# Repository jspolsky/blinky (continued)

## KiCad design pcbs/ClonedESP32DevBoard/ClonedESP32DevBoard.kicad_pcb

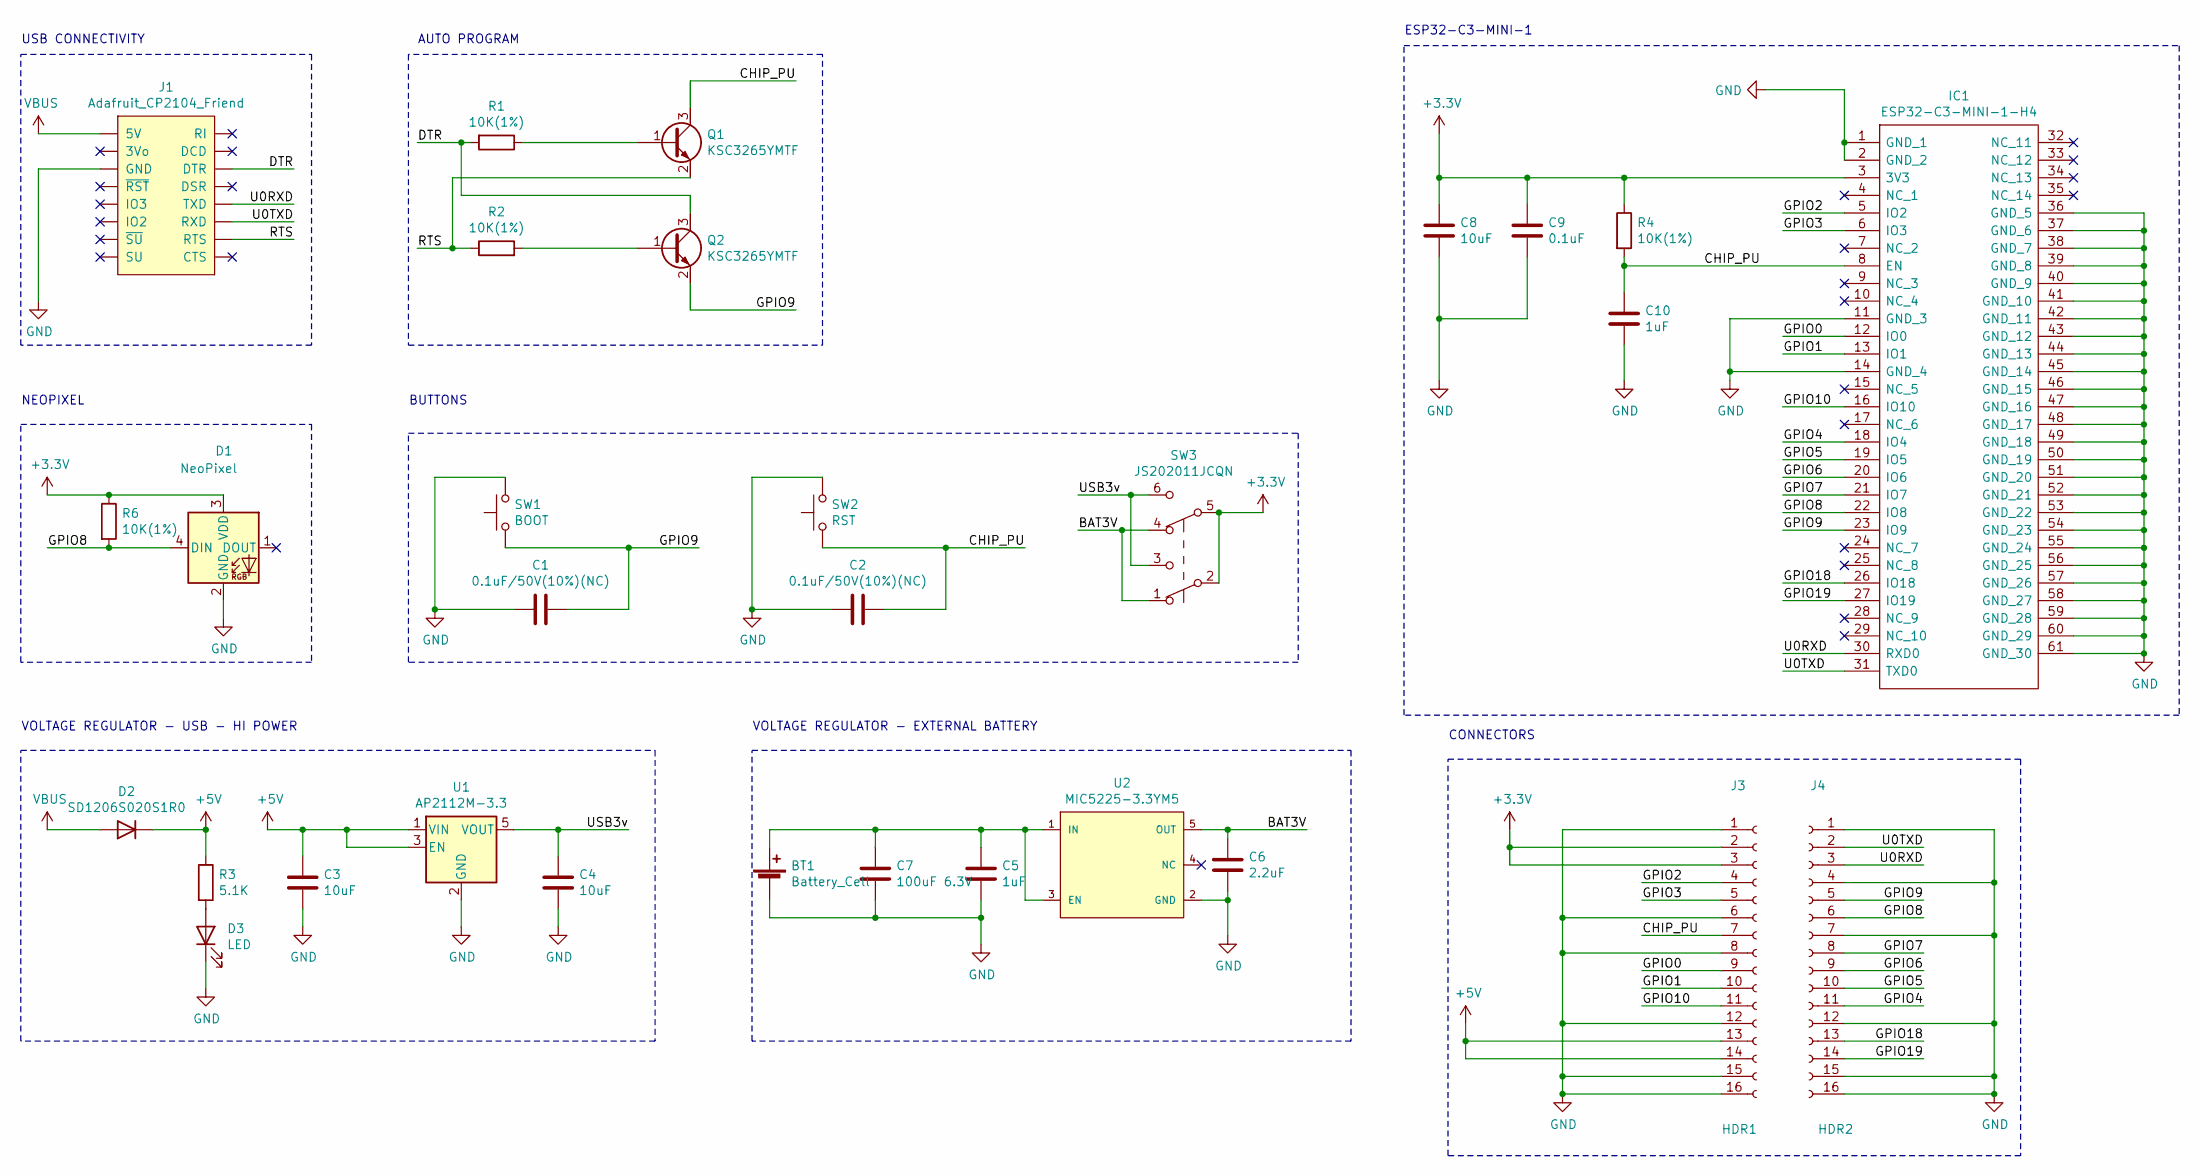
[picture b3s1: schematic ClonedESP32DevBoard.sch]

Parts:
BT1: Battery_Cell; PinHeader_1x02_P2.54mm_Vertical
C1, C2: 0.1uF/50V(10%)(NC); C_0805_2012Metric
C3, C4, C8: 10uF; C_0805_2012Metric
C5, C10: 1uF; C_0805_2012Metric
C6: 2.2uF; C_0805_2012Metric
C7: 100uF 6.3V; C_1210_3225Metric
C9: 0.1uF; C_0805_2012Metric
D1: NeoPixel; LED_WS2812-2020
D2: SD1206S020S1R0‎; D_1206_3216Metric
D3: LED; LED_0805_2012Metric
IC1: ESP32-C3-MINI-1-H4; ESP32-C3-MINI-1; Manufacturer_Part_Number ESP32-C3-MINI-1-H4; Mouser Part Number 356-ESP32-C3-MINI1H4
J1: Adafruit_CP2104_Friend
J3: HDR1; PinHeader_1x16_P2.54mm_Vertical
J4: HDR2; PinHeader_1x16_P2.54mm_Vertical
Q1, Q2: KSC3265YMTF; SOT-23
R1, R2, R4, R6: 10K(1%); R_0805_2012Metric
R3: 5.1K; R_0805_2012Metric
SW1: BOOT; TL9320AF400QG
SW2: RST; TL9320AF400QG
SW3: JS202011JCQN; SW_DPDT_CK_JS202011JCQN
U1: AP2112M-3.3; Diodes-SO-8
U2: MIC5225-3.3YM5; MIC5225-SOT23-5LD; dropout voltage 310mV; output voltage 3.3V; mouser part number 998-MIC5225-3.3YM5TR; digikey description IC REG LINEAR 3.3V 150MA SOT23-5

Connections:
+3V3: C8.1, C9.1, D1.3 (VDD), IC1.3 (3V3), J3.2, J3.3, R4.1, R6.1, SW3.2 (B), SW3.5 (B)
+5V: C3.1, D2.1 (K), J3.13, J3.14, R3.1, U1.1 (VIN), U1.3 (EN)
/BAT3V: C6.1, SW3.1 (A), SW3.4 (A), U2.5 (OUT)
/CHIP_PU: C2.1, C10.1, IC1.8 (EN), J3.7, Q1.3 (C), R4.2, SW2.1
/DTR: J1.14 (DTR), Q2.3 (C), R1.2
/GPIO0: IC1.12 (IO0), J3.9
/GPIO1: IC1.13 (IO1), J3.10
/GPIO2: IC1.5 (IO2), J3.4
/GPIO3: IC1.6 (IO3), J3.5
/GPIO4: IC1.18 (IO4), J4.11
/GPIO5: IC1.19 (IO5), J4.10
/GPIO6: IC1.20 (IO6), J4.9
/GPIO7: IC1.21 (IO7), J4.8
/GPIO8: D1.4 (DIN), IC1.22 (IO8), J4.6, R6.2
/GPIO9: C1.1, IC1.23 (IO9), J4.5, Q2.2 (E), SW1.1
/GPIO10: IC1.16 (IO10), J3.11
/GPIO18: IC1.26 (IO18), J4.13
/GPIO19: IC1.27 (IO19), J4.14
/RTS: J1.10 (RTS), Q1.2 (E), R2.1
/U0RXD: IC1.30 (RXD0), J1.12 (TXD), J4.3
/U0TXD: IC1.31 (TXD0), J1.11 (RXD), J4.2
/USB3v: C4.1, SW3.3 (C), SW3.6 (C), U1.5 (VOUT)
GND: BT1.2 (-), C1.2, C2.2, C3.2, C4.2, C5.2, C6.2, C7.2, C8.2, C9.2, C10.2, D1.2 (GND), D3.1 (K), IC1.1 (GND_1), IC1.2 (GND_2), IC1.11 (GND_3), IC1.14 (GND_4), IC1.36 (GND_5), IC1.37 (GND_6), IC1.38 (GND_7), IC1.39 (GND_8), IC1.40 (GND_9), IC1.41 (GND_10), IC1.42 (GND_11), IC1.43 (GND_12), IC1.44 (GND_13), IC1.45 (GND_14), IC1.46 (GND_15), IC1.47 (GND_16), IC1.48 (GND_17), IC1.49 (GND_18), IC1.50 (GND_19), IC1.51 (GND_20), IC1.52 (GND_21), IC1.53 (GND_22), IC1.54 (GND_23), IC1.55 (GND_24), IC1.56 (GND_25), IC1.57 (GND_26), IC1.58 (GND_27), IC1.59 (GND_28), IC1.60 (GND_29), IC1.61 (GND_30), J1.3 (GND), J3.1, J3.6, J3.8, J3.12, J3.15, J3.16, J4.1, J4.4, J4.7, J4.12, J4.15, J4.16, SW1.2, SW2.2, U1.2 (GND), U2.2 (GND)
unnamed: BT1.1 (+), C5.1, C7.1, U2.1 (IN), U2.3 (EN)
unnamed: D3.2 (A), R3.2
unnamed: Q1.1 (B), R1.1
unnamed: Q2.1 (B), R2.2
VBUS: D2.2 (A), J1.1 (5V)

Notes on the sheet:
USB CONNECTIVITY
AUTO PROGRAM
NEOPIXEL
BUTTONS
VOLTAGE REGULATOR - USB - HI POWER
VOLTAGE REGULATOR - EXTERNAL BATTERY
ESP32-C3-MINI-1
CONNECTORS

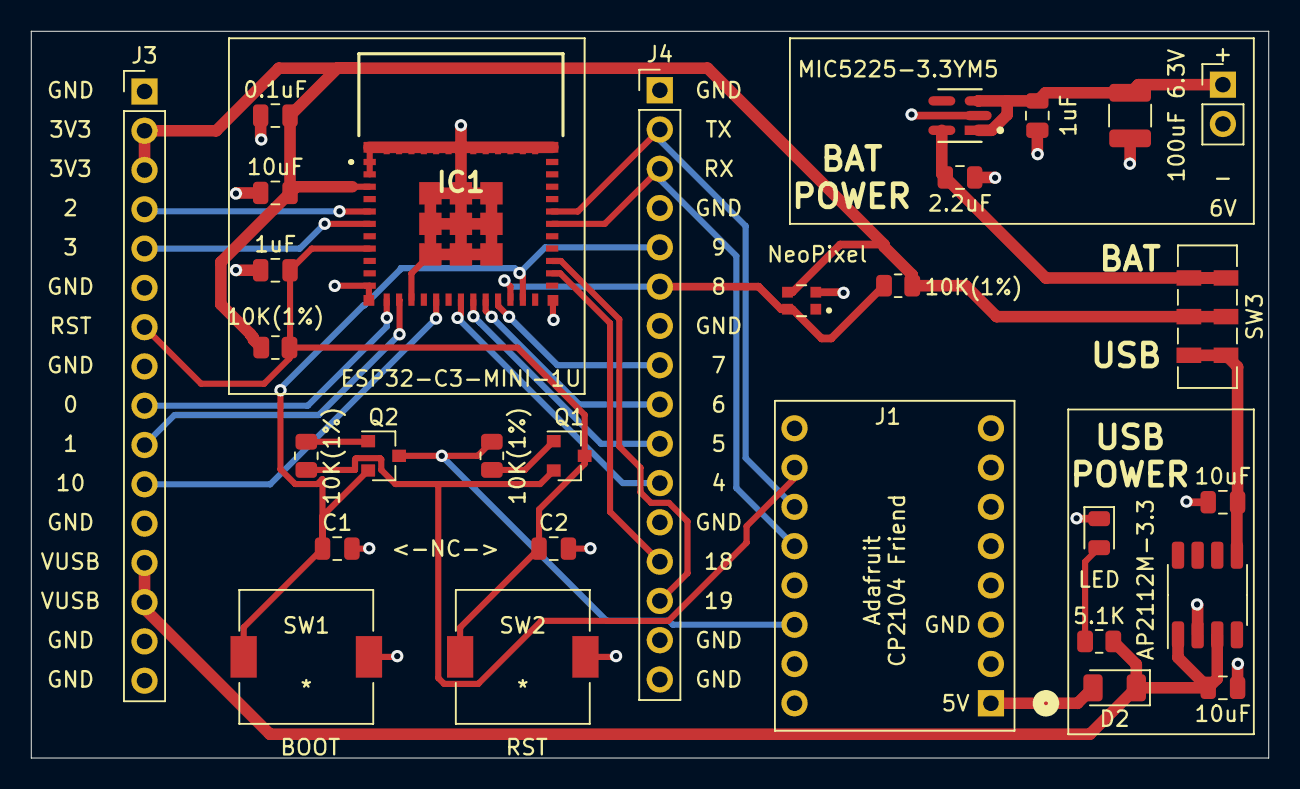
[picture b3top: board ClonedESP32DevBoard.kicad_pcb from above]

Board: 2 copper layers, 80.0 x 47.0 mm, 30 parts (0 on the bottom side), 28 nets.

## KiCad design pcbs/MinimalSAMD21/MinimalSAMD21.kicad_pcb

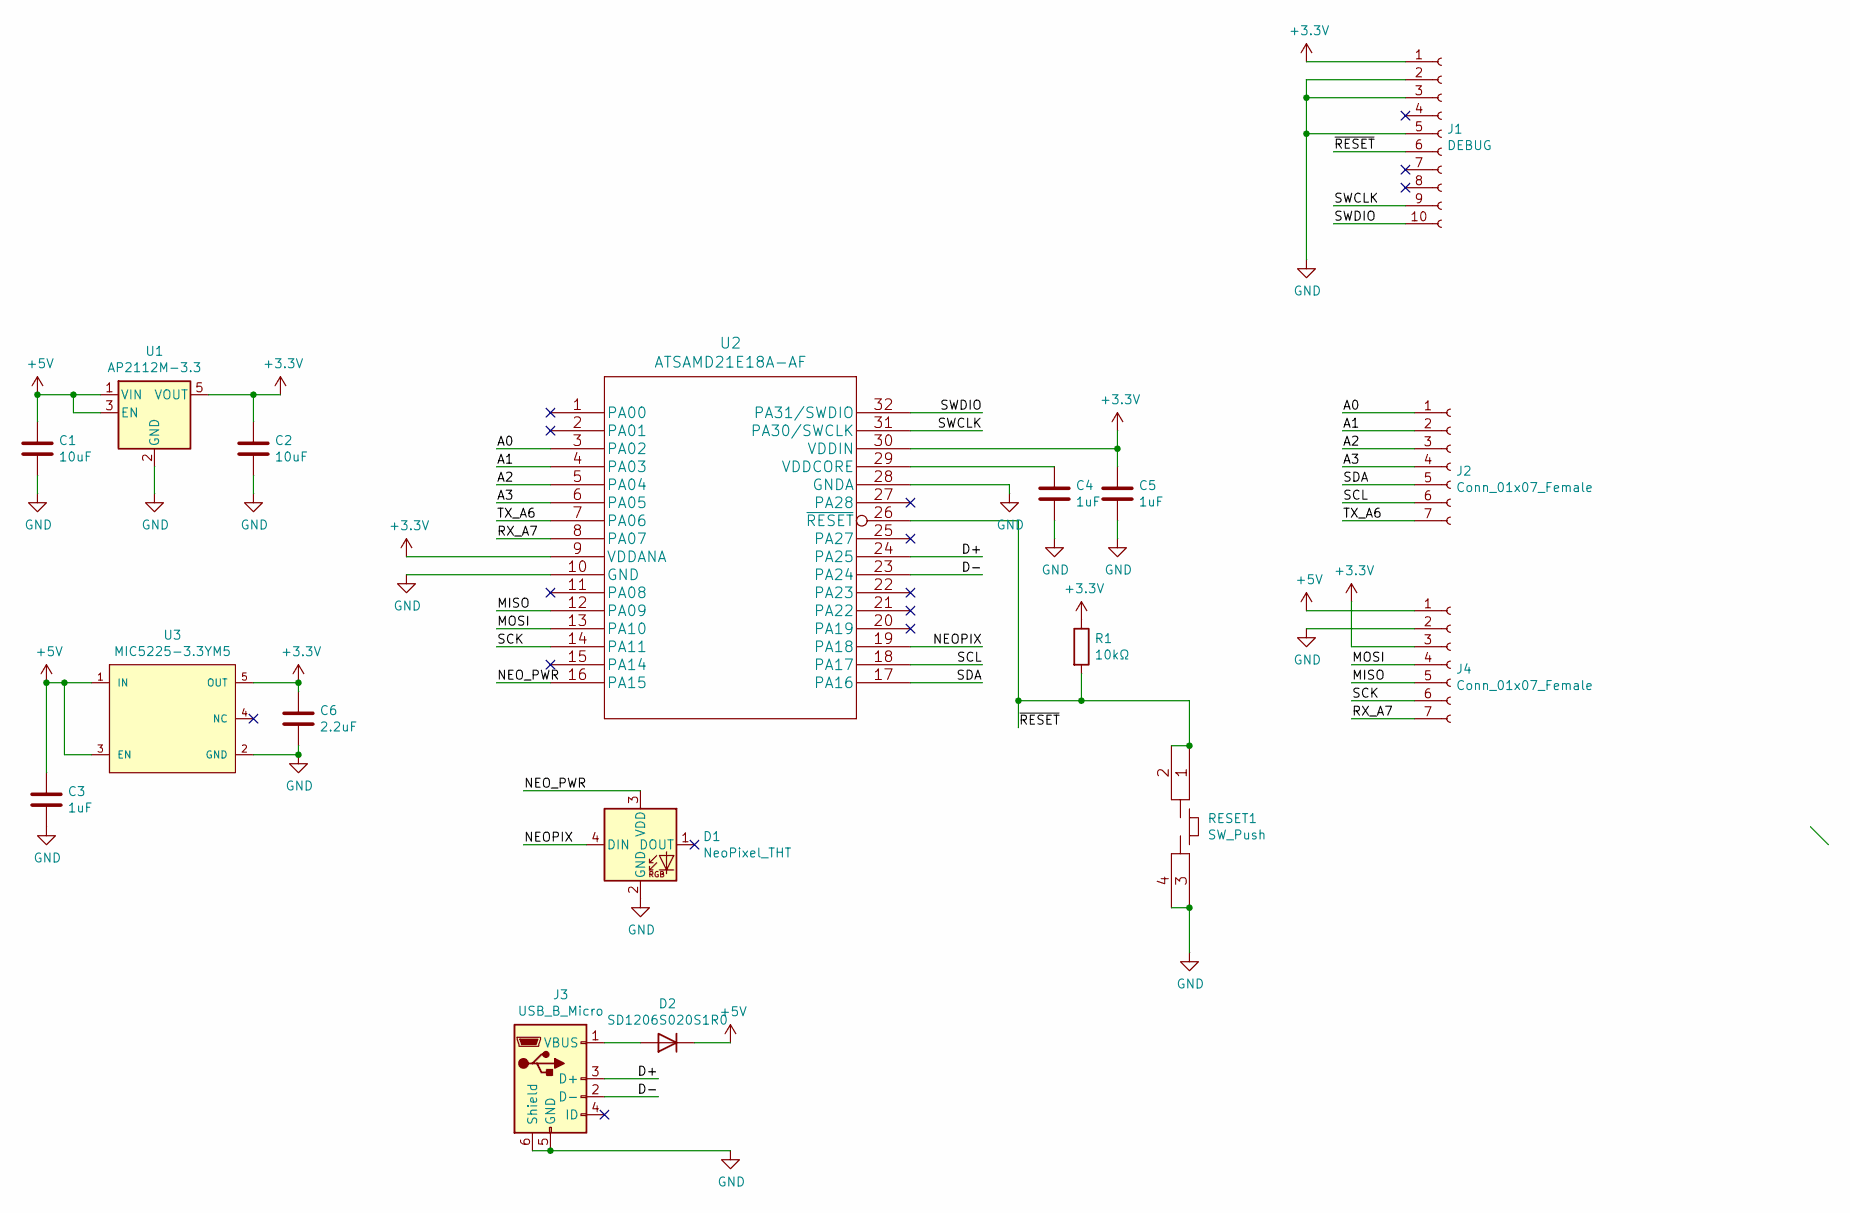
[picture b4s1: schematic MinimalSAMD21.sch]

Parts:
C1, C2: 10uF; C_0805_2012Metric_Pad1.18x1.45mm_HandSolder
C3, C4, C5: 1uF; C_0805_2012Metric_Pad1.18x1.45mm_HandSolder
C6: 2.2uF; C_0805_2012Metric_Pad1.18x1.45mm_HandSolder
D1: NeoPixel_THT; LED_WS2812-2020
D2: SD1206S020S1R0‎; D_1206_3216Metric
J1: DEBUG; CNC_3220-10-0300-00_SWD_Receptacle
J2, J4: Conn_01x07_Female; PinSocket_1x07_P2.54mm_Vertical
J3: USB_B_Micro; USB_Micro-B_Amphenol_10118194_Horizontal
R1: 10kΩ; R_0805_2012Metric_Pad1.20x1.40mm_HandSolder
RESET1: SW_Push; PTS526_SK15_SMTR2_LFS_Tactile_SW_5.2x5.2
U1: AP2112M-3.3; Diodes-SO-8
U2: ATSAMD21E18A-AF
U3: MIC5225-3.3YM5; MIC5225-SOT23-5LD; dropout voltage 310mV; output voltage 3.3V; mouser part number 998-MIC5225-3.3YM5TR; digikey description IC REG LINEAR 3.3V 150MA SOT23-5

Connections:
+3V3: C2.1, C5.1, C6.1, J1.1, J4.3, R1.1, U1.5 (VOUT), U2.9 (VDDANA), U2.30 (VDDIN), U3.5 (OUT); also elsewhere on the board
+5V: C1.1, C3.1, D2.1 (K), J4.1, U1.1 (VIN), U1.3 (EN), U3.1 (IN), U3.3 (EN)
/A0: J2.1, U2.3 (PA02)
/A1: J2.2, U2.4 (PA03)
/A2: J2.3, U2.5 (PA04)
/A3: J2.4, U2.6 (PA05)
/D+: J3.3 (D+), U2.24 (PA25)
/D-: J3.2 (D-), U2.23 (PA24)
/MISO: J4.5, U2.12 (PA09)
/MOSI: J4.4, U2.13 (PA10)
/NEOPIX: D1.4 (DIN), U2.19 (PA18)
/NEO_PWR: D1.3 (VDD), U2.16 (PA15)
/RX_A7: J4.7, U2.8 (PA07)
/SCK: J4.6, U2.14 (PA11)
/SCL: J2.6, U2.18 (PA17)
/SDA: J2.5, U2.17 (PA16)
/SWCLK: J1.9, U2.31 (PA30/SWCLK); also elsewhere on the board
/SWDIO: J1.10, U2.32 (PA31/SWDIO); also elsewhere on the board
/TX_A6: J2.7, U2.7 (PA06)
/~RESET: J1.6, R1.2, RESET1.1, RESET1.2, U2.26 (~RESET); also elsewhere on the board
GND: C1.2, C2.2, C3.2, C4.2, C5.2, C6.2, D1.2 (GND), J1.2, J1.3, J1.5, J3.5 (GND), J3.6 (Shield), J4.2, RESET1.3, RESET1.4, U1.2 (GND), U2.10 (GND), U2.28 (GNDA), U3.2 (GND); also elsewhere on the board
unnamed: C4.1, U2.29 (VDDCORE)
unnamed: D2.2 (A), J3.1 (VBUS)

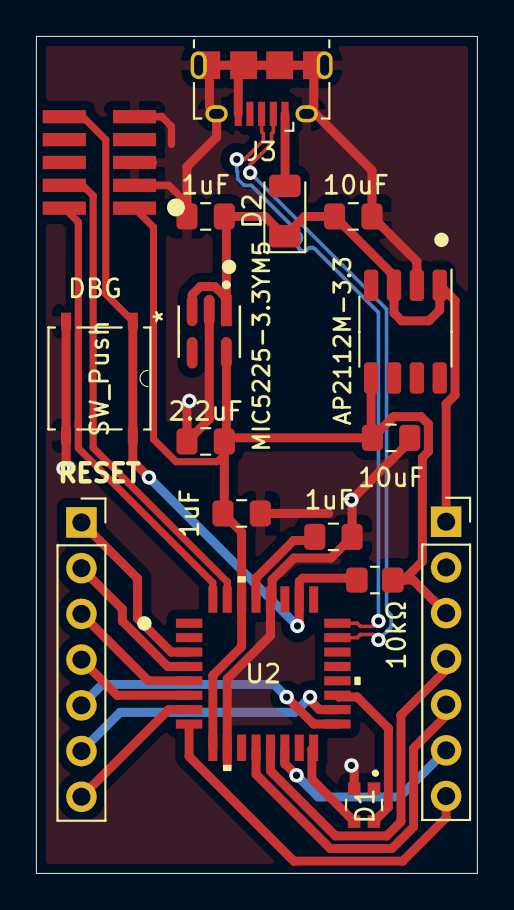
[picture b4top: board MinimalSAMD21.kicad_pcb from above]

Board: 2 copper layers, 24.5 x 46.5 mm, 17 parts (0 on the bottom side), 23 nets.

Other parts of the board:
DBG: DEBUG; CNC_3220-10-0300-00_SWD_Receptacle

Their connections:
+3V3: DBG.1; also elsewhere on the board
/SWCLK: DBG.9; also elsewhere on the board
/SWDIO: DBG.10; also elsewhere on the board
/~RESET: DBG.6; also elsewhere on the board
GND: DBG.2, DBG.3, DBG.5; also elsewhere on the board

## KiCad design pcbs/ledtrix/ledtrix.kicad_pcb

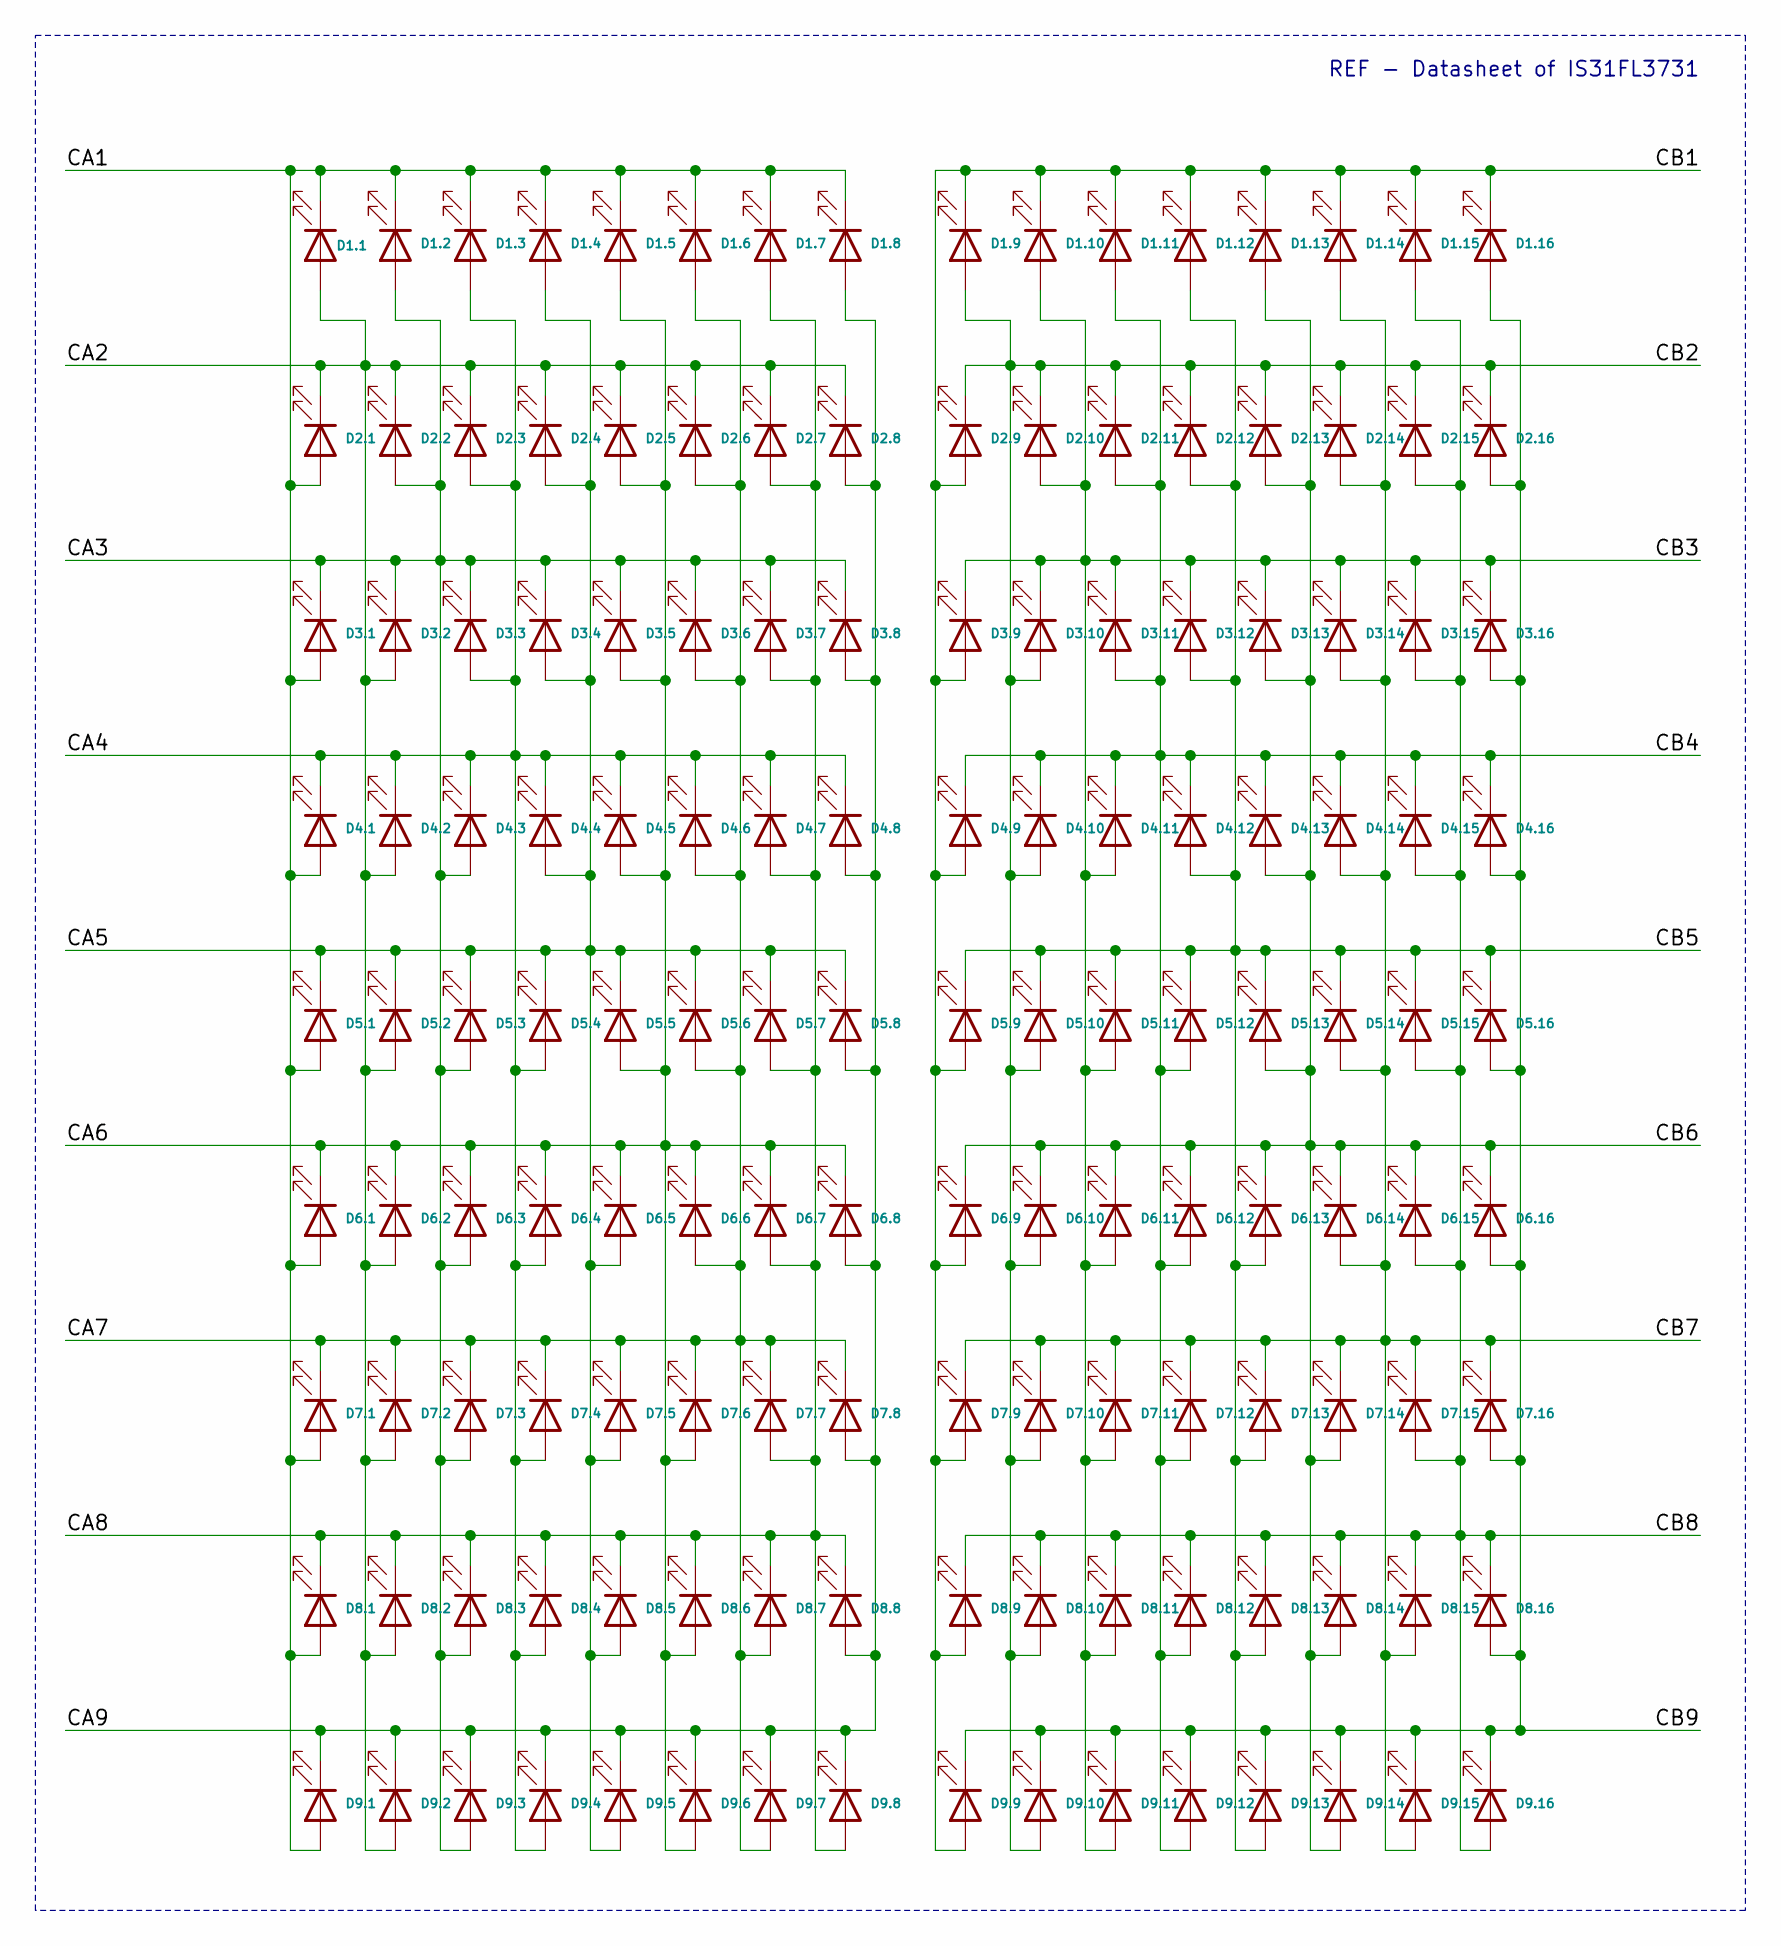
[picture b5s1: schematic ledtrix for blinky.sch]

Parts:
D1.1, D1.2, D1.3, D1.4, D1.5, D1.6, D1.7, D1.8, D1.9, D1.10, D1.11, D1.12, D1.13, D1.14, D1.15, D1.16, D2.1, D2.2, D2.3, D2.4, D2.5, D2.6, D2.7, D2.8, D2.9, D2.10, D2.11, D2.12, D2.13, D2.14, D2.15, D2.16, D3.1, D3.2, D3.3, D3.4, D3.5, D3.6, D3.7, D3.8, D3.9, D3.10, D3.11, D3.12, D3.13, D3.14, D3.15, D3.16, D4.1, D4.2, D4.3, D4.4, D4.5, D4.6, D4.7, D4.8, D4.9, D4.10, D4.11, D4.12, D4.13, D4.14, D4.15, D4.16, D5.1, D5.2, D5.3, D5.4, D5.5, D5.6, D5.7, D5.8, D5.9, D5.10, D5.11, D5.12, D5.13, D5.14, D5.15, D5.16, D6.1, D6.2, D6.3, D6.4, D6.5, D6.6, D6.7, D6.8, D6.9, D6.10, D6.11, D6.12, D6.13, D6.14, D6.15, D6.16, D7.1, D7.2, D7.3, D7.4, D7.5, D7.6, D7.7, D7.8, D7.9, D7.10, D7.11, D7.12, D7.13, D7.14, D7.15, D7.16, D8.1, D8.2, D8.3, D8.4, D8.5, D8.6, D8.7, D8.8, D8.9, D8.10, D8.11, D8.12, D8.13, D8.14, D8.15, D8.16, D9.1, D9.2, D9.3, D9.4, D9.5, D9.6, D9.7, D9.8, D9.9, D9.10, D9.11, D9.12, D9.13, D9.14, D9.15, D9.16: LED; LED_0603_For_Blinky

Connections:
/CA1: D1.1.1 (K), D1.2.1 (K), D1.3.1 (K), D1.4.1 (K), D1.5.1 (K), D1.6.1 (K), D1.7.1 (K), D1.8.1 (K), D2.1.2 (A), D3.1.2 (A), D4.1.2 (A), D5.1.2 (A), D6.1.2 (A), D7.1.2 (A), D8.1.2 (A), D9.1.2 (A); also elsewhere on the board
/CA2: D1.1.2 (A), D2.1.1 (K), D2.2.1 (K), D2.3.1 (K), D2.4.1 (K), D2.5.1 (K), D2.6.1 (K), D2.7.1 (K), D2.8.1 (K), D3.2.2 (A), D4.2.2 (A), D5.2.2 (A), D6.2.2 (A), D7.2.2 (A), D8.2.2 (A), D9.2.2 (A); also elsewhere on the board
/CA3: D1.2.2 (A), D2.2.2 (A), D3.1.1 (K), D3.2.1 (K), D3.3.1 (K), D3.4.1 (K), D3.5.1 (K), D3.6.1 (K), D3.7.1 (K), D3.8.1 (K), D4.3.2 (A), D5.3.2 (A), D6.3.2 (A), D7.3.2 (A), D8.3.2 (A), D9.3.2 (A); also elsewhere on the board
/CA4: D1.3.2 (A), D2.3.2 (A), D3.3.2 (A), D4.1.1 (K), D4.2.1 (K), D4.3.1 (K), D4.4.1 (K), D4.5.1 (K), D4.6.1 (K), D4.7.1 (K), D4.8.1 (K), D5.4.2 (A), D6.4.2 (A), D7.4.2 (A), D8.4.2 (A), D9.4.2 (A); also elsewhere on the board
/CA5: D1.4.2 (A), D2.4.2 (A), D3.4.2 (A), D4.4.2 (A), D5.1.1 (K), D5.2.1 (K), D5.3.1 (K), D5.4.1 (K), D5.5.1 (K), D5.6.1 (K), D5.7.1 (K), D5.8.1 (K), D6.5.2 (A), D7.5.2 (A), D8.5.2 (A), D9.5.2 (A); also elsewhere on the board
/CA6: D1.5.2 (A), D2.5.2 (A), D3.5.2 (A), D4.5.2 (A), D5.5.2 (A), D6.1.1 (K), D6.2.1 (K), D6.3.1 (K), D6.4.1 (K), D6.5.1 (K), D6.6.1 (K), D6.7.1 (K), D6.8.1 (K), D7.6.2 (A), D8.6.2 (A), D9.6.2 (A); also elsewhere on the board
/CA7: D1.6.2 (A), D2.6.2 (A), D3.6.2 (A), D4.6.2 (A), D5.6.2 (A), D6.6.2 (A), D7.1.1 (K), D7.2.1 (K), D7.3.1 (K), D7.4.1 (K), D7.5.1 (K), D7.6.1 (K), D7.7.1 (K), D7.8.1 (K), D8.7.2 (A), D9.7.2 (A); also elsewhere on the board
/CA8: D1.7.2 (A), D2.7.2 (A), D3.7.2 (A), D4.7.2 (A), D5.7.2 (A), D6.7.2 (A), D7.7.2 (A), D8.1.1 (K), D8.2.1 (K), D8.3.1 (K), D8.4.1 (K), D8.5.1 (K), D8.6.1 (K), D8.7.1 (K), D8.8.1 (K), D9.8.2 (A); also elsewhere on the board
/CA9: D1.8.2 (A), D2.8.2 (A), D3.8.2 (A), D4.8.2 (A), D5.8.2 (A), D6.8.2 (A), D7.8.2 (A), D8.8.2 (A), D9.1.1 (K), D9.2.1 (K), D9.3.1 (K), D9.4.1 (K), D9.5.1 (K), D9.6.1 (K), D9.7.1 (K), D9.8.1 (K); also elsewhere on the board
/CB1: D1.9.1 (K), D1.10.1 (K), D1.11.1 (K), D1.12.1 (K), D1.13.1 (K), D1.14.1 (K), D1.15.1 (K), D1.16.1 (K), D2.9.2 (A), D3.9.2 (A), D4.9.2 (A), D5.9.2 (A), D6.9.2 (A), D7.9.2 (A), D8.9.2 (A), D9.9.2 (A); also elsewhere on the board
/CB2: D1.9.2 (A), D2.9.1 (K), D2.10.1 (K), D2.11.1 (K), D2.12.1 (K), D2.13.1 (K), D2.14.1 (K), D2.15.1 (K), D2.16.1 (K), D3.10.2 (A), D4.10.2 (A), D5.10.2 (A), D6.10.2 (A), D7.10.2 (A), D8.10.2 (A), D9.10.2 (A); also elsewhere on the board
/CB3: D1.10.2 (A), D2.10.2 (A), D3.9.1 (K), D3.10.1 (K), D3.11.1 (K), D3.12.1 (K), D3.13.1 (K), D3.14.1 (K), D3.15.1 (K), D3.16.1 (K), D4.11.2 (A), D5.11.2 (A), D6.11.2 (A), D7.11.2 (A), D8.11.2 (A), D9.11.2 (A); also elsewhere on the board
/CB4: D1.11.2 (A), D2.11.2 (A), D3.11.2 (A), D4.9.1 (K), D4.10.1 (K), D4.11.1 (K), D4.12.1 (K), D4.13.1 (K), D4.14.1 (K), D4.15.1 (K), D4.16.1 (K), D5.12.2 (A), D6.12.2 (A), D7.12.2 (A), D8.12.2 (A), D9.12.2 (A); also elsewhere on the board
/CB5: D1.12.2 (A), D2.12.2 (A), D3.12.2 (A), D4.12.2 (A), D5.9.1 (K), D5.10.1 (K), D5.11.1 (K), D5.12.1 (K), D5.13.1 (K), D5.14.1 (K), D5.15.1 (K), D5.16.1 (K), D6.13.2 (A), D7.13.2 (A), D8.13.2 (A), D9.13.2 (A); also elsewhere on the board
/CB6: D1.13.2 (A), D2.13.2 (A), D3.13.2 (A), D4.13.2 (A), D5.13.2 (A), D6.9.1 (K), D6.10.1 (K), D6.11.1 (K), D6.12.1 (K), D6.13.1 (K), D6.14.1 (K), D6.15.1 (K), D6.16.1 (K), D7.14.2 (A), D8.14.2 (A), D9.14.2 (A); also elsewhere on the board
/CB7: D1.14.2 (A), D2.14.2 (A), D3.14.2 (A), D4.14.2 (A), D5.14.2 (A), D6.14.2 (A), D7.9.1 (K), D7.10.1 (K), D7.11.1 (K), D7.12.1 (K), D7.13.1 (K), D7.14.1 (K), D7.15.1 (K), D7.16.1 (K), D8.15.2 (A), D9.15.2 (A); also elsewhere on the board
/CB8: D1.15.2 (A), D2.15.2 (A), D3.15.2 (A), D4.15.2 (A), D5.15.2 (A), D6.15.2 (A), D7.15.2 (A), D8.9.1 (K), D8.10.1 (K), D8.11.1 (K), D8.12.1 (K), D8.13.1 (K), D8.14.1 (K), D8.15.1 (K), D8.16.1 (K), D9.16.2 (A); also elsewhere on the board
/CB9: D1.16.2 (A), D2.16.2 (A), D3.16.2 (A), D4.16.2 (A), D5.16.2 (A), D6.16.2 (A), D7.16.2 (A), D8.16.2 (A), D9.9.1 (K), D9.10.1 (K), D9.11.1 (K), D9.12.1 (K), D9.13.1 (K), D9.14.1 (K), D9.15.1 (K), D9.16.1 (K); also elsewhere on the board

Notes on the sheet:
REF - Datasheet of IS31FL3731

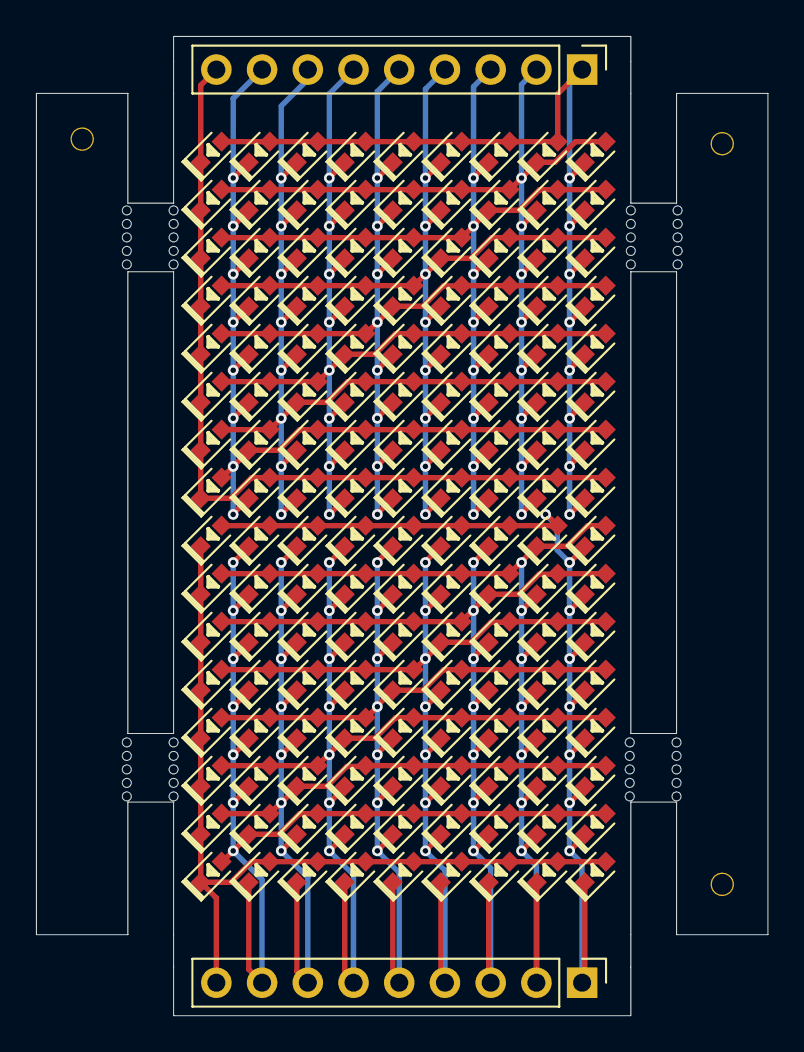
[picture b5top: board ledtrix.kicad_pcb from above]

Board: 2 copper layers, 40.6 x 54.4 mm, 153 parts (0 on the bottom side), 18 nets.

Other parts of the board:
H1, H2, H4, H5: Mousebites; Mouse_Bite_For_Clipper
H7, H8, H9: MountingHole; JCLPCB_Tooling_Hole
J1, J2: Conn; PinHeader_1x09_P2.54mm_Vertical

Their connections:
/CA1: J1.1; also elsewhere on the board
/CA2: J1.2; also elsewhere on the board
/CA3: J1.3; also elsewhere on the board
/CA4: J1.4; also elsewhere on the board
/CA5: J1.5; also elsewhere on the board
/CA6: J1.6; also elsewhere on the board
/CA7: J1.7; also elsewhere on the board
/CA8: J1.8; also elsewhere on the board
/CA9: J1.9; also elsewhere on the board
/CB1: J2.1; also elsewhere on the board
/CB2: J2.2; also elsewhere on the board
/CB3: J2.3; also elsewhere on the board
/CB4: J2.4; also elsewhere on the board
/CB5: J2.5; also elsewhere on the board
/CB6: J2.6; also elsewhere on the board
/CB7: J2.7; also elsewhere on the board
/CB8: J2.8; also elsewhere on the board
/CB9: J2.9; also elsewhere on the board

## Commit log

2021-10-08 testing github setup
2021-10-11 new, dimmer animation for testing with
2021-10-11 Switch to ArduinoLowPower library. Add button.
2021-10-11 constant color
2021-10-11 working button press with and without wakeup
2021-10-11 JUST STAY ASLEEP OK?
2021-10-11 turn off status LED while measuring batt life
2021-10-11 started working on Infrared. Sleep is commented out
2021-10-12 Code for a simple Gemma M0 tester
2021-10-12 Testing IR receiving. And it's going well.
2021-10-12 wakes up on IR receive! (Doesn't go back to sleep ever)
2021-10-12 Starting to modularize. Ledmatrix.
2021-10-13 continuing to modularize
2021-10-13 extra headers weren't being used
2021-10-13 Button code moved out
2021-10-13 Final cleanups and modularization
2021-10-13 go back to sleep after any activity
2021-10-13 ready to control power to IR receiver from a pin
2021-10-13 Not going to use MCU to blink the ir receiver, it's too power consumptive
2021-10-14 Button "click" is working with debounce
2021-10-14 All the button logic is sorted out!
2021-10-16 implement showChar to help debugging the next phase
2021-10-27 scaffolding for animation inventory manager
2021-11-03 IR debugging device (receive only)
2021-11-03 pin for IR sending
2021-11-03 IR receiver no longer runs nonstop
2021-11-03 Separation of concerns
2021-11-03 cleanup from last commit
2021-11-03 renamed IR functions
2021-11-03 button control pass through to IR
2021-11-03 was repeating long click message instead of sending once
2021-11-03 actually send a code
2021-11-04 comment out sending for now
2021-11-04 onboard neopixel is for button state debugging
2021-11-04 use a bit of a state machine with loop()
2021-11-04 listen after sending
2021-11-04 use blue for reasons
2021-11-04 full protocol state machine done
2021-11-04 power off ir receiver when not in use
2021-11-05 pause without delay(), tweaks
2021-11-05 keep going after button lifted; always end protocol after 30s
2021-11-05 obsolete bitmap
2021-11-10 exhcange-in-progress animation
2021-11-10 parsepng improved to handle different number of frames
2021-11-10 this wasn't in use
2021-11-10 ability to have animations of different lengths
2021-11-10 animations of different lengths
2021-11-10 tweaking the greyscale / gamma correction
2021-11-10 flip 9x16 to 16x9 in the .h file so we can pack two pixels in a byte later
2021-11-11 compress each pixel into a single nibble
2021-11-11 comment was out of date
2021-11-11 short click now actually changes animation
2021-11-11 slight cleanups to better interpret button clicks
2021-11-11 go back to current animation when done
2021-11-11 Some tweaking of button logic for fewer confused clicks
2021-11-11 an array of animations!
2021-11-11 show greyscales - for debugging power consumption
2021-11-11 ParsePng can now estimate mA usage per animation
2021-11-11 show the special animation while in IR xchange
2021-11-11 15 seconds should be long enough to run the protocol if you've dropped the ball
2021-11-11 stuff
2021-11-11 very rudimentary flash storage!
2021-11-11 pick my animation at random on first flash
2021-11-12 Inventory storage actually works!
2021-11-12 ignore .DS_Store
2021-11-12 full swap is working
2021-11-21 new man
2021-11-21 man better base
2021-11-21 man stick legs
2021-11-23 stupid .DS_Store what is that anyway
2021-11-23 we have a bom (but it's in google)
2021-11-23 added ben's animation
2021-11-23 Using RTC for PowerSave - scaffold
2021-11-23 PowerSave at 2 hrs implemented! Needs more test
2021-11-26 pong!
2021-11-27 Schematic and PCB design - 90%
2021-12-01 blinky version 1 PCB design is done!
2021-12-01 this version was submitted to pcbway
2021-12-06 Gerbers for first prototype production
2021-12-10 simple test code to get minimal samd board working
2021-12-10 new design for minimal SAMD21 board
2021-12-10 PREVIEW blinky shows animations fed through USB
2021-12-10 Progress adapting blinky code to support previews
2021-12-11 mostly got preview working
2021-12-11 indicator light
2021-12-18 experimenting with turtle shaped PCB
2021-12-18 my own ESP32C3 development board
2021-12-18 my own Charlieplex board
2021-12-18 moved blinky to blinky (arm) and starting to rewrite for esp32c3
2021-12-18 the file structure I like works in Arduino IDE
2021-12-18 Button operation working (without sleep mode)
2021-12-18 added a pull-up resistor so deep sleep uses less power
2021-12-18 press button to wake up from deep sleep
2021-12-19 change color on click
2021-12-19 esp32 in arduino IDE experiment
2021-12-19 Handy ESP32-C3-DevKitM-1 tester
2021-12-19 Using ws2812bRainbowEsp32 as template for blinky IDF
2021-12-19 Deep sleep; pin 2 wakeup! it's fast!!
2021-12-19 move rgbled out into it's own file
2021-12-19 beginning of button logic
2021-12-19 short and long press logic
2021-12-20 long press starts sooner
2021-12-20 a little structure
2021-12-20 programming by wishful thinking
2021-12-20 more programming by wishful thinking
2021-12-20 just move my button off of the strapping pin why i don't know
2021-12-20 implemented a little function to write things to i2c.
2021-12-20 YAY! CHARLIEPLEX IS MINE!
2021-12-20 slo tho
2021-12-20 much faster load animation
2021-12-21 parsepng now dumps binary blobs
2021-12-21 reasonable approximation of animation loaded
2021-12-21 OMIGOD OMIGOD OMIGOD animation works again tg
2021-12-21 fixed so it works at power up
2021-12-22 IR sending is working!
2021-12-22 progress on receiving data as well as sending it!
2021-12-22 inventory probably completely working
2021-12-22 a little reorging the animation sequence
2021-12-22 remember current animation and inventory on wakeup from deep sleep
2021-12-22 remove debugging code
2021-12-23 rename functions
2021-12-23 structure around exchange button
2021-12-23 "send" part of the protocol - done!
2021-12-23 send and receive all at the same time lol
2021-12-23 first successful receive!!!
2021-12-23 inventory reset button! press it while booting up
2021-12-24 move animation to Task
2021-12-24 IR: use queue to notify main task to add received animation
2021-12-24 don't need to display animations on a thread anymore
2021-12-24 a lot of charlieplex initialization wasn't doing anything at all
2021-12-24 turn off exchange animation when done
2021-12-24 Revert "a lot of charlieplex initialization wasn't doing anything at all"
    This reverts commit d0891acefc49ccd1926b55f96ddce0c56e2a193e.
2021-12-24 don't initialize charlieplex after first power up
2021-12-24 Power off IR receiver when not in use, power off screen too
2021-12-24 click to wake up does not increment animation
2021-12-24 power off screen after 2 hours
2021-12-24 readme
2021-12-26 why is kicad so annoying
2021-12-27 getting ARM working again
2021-12-27 LED-only PCB situation
2021-12-27 Make some boards with just the LEDs
2021-12-27 Updated blinky schematic (ARM) for latest technology
2021-12-27 started work on the pcb
2021-12-28 routing this board here
2021-12-28 making good progress on the circuit board
2021-12-28 flash with jlink
2021-12-29 Everything is done except artistic stuff
2021-12-30 Moved power switch up to make board shorter
2021-12-30 some 3d models
2021-12-30 Put all the passive values on silkscreen
2021-12-30 route sda/scl across the middle
2021-12-30 tidied up a bit more routing to make board smaller
2021-12-30 lots of beautiful decorations
2021-12-30 mousebite improvements
2021-12-31 lovely logo
2021-12-31 more details
2021-12-31 ok, well that has been sent to china
2022-01-01 restored C code generation in parsepng
2022-01-01 much wonderful cleanup of matrix inventory handling
2022-01-01 reusable "shutdown"
2022-01-01 blank screen while writing
2022-01-01 much faster animation display
2022-01-01 unflipped image
2022-01-01 clean sample code showing new power management scheme
2022-01-01 new power management code perfected
2022-01-01 bug crept in
2022-01-01 Hold A7 low at startup to reset inventory
2022-01-02 test pattern on animation reset
2022-01-02 rewritten low power logic! clean!
2022-01-02 slight refactoring to clean up IR protocol
2022-01-02 slightly shorter protocol to save power
2022-01-02 remove unused functions
2022-01-02 correct recovery after power up
2022-01-02 clean up unused stuff, screen off during init
2022-01-02 stripped out unused GFX library
2022-01-02 badly named variable
2022-01-03 generated a 3D file for PCB
2022-01-03 temporary lower brightness for _exchange (still needs work)
2022-01-03 Use 100K resistor for Rext to save power
2022-01-03 2hr screen saver
2022-01-04 renamed a folder to avoid confusion
2022-01-04 updating parsepng
2022-01-04 fixed a little off by one bug
2022-01-04 line up formatted .h file
2022-01-04 some preview cleanup
2022-01-04 this didn't work
2022-01-04 initial errors sending to serial -> fixed!
2022-01-04 "watch" is probably working now (not tested tho)
2022-01-05 some things don't have to be in the code
2022-01-05 oops!
2022-01-05 don't need to generate .bin files any more, that was for esp32
2022-01-05 New amp consumption based on 100k Rext
2022-01-05 Display "thermometer" of estimated mA usage including being judgy
2022-01-05 exchange is a little dimmer
2022-01-05 always generate .h file, always preview
2022-01-06 save a ton of power
2022-01-07 new protocol seems to save about 2.5-5 mA?
2022-01-07 slightly shorter protocol
2022-01-07 strip out old protocol code
2022-01-07 lower power usage waiting on button
2022-01-07 one last optimization
2022-01-07 sorry gotta use dimmer exchange animation
2022-01-08 I like this "exchange" animation better
2022-01-09 new lightning animation
2022-01-10 six lovely new animations
2022-01-10 more centered
2022-02-21 Updated schematics and PCB to fix all known bugs
